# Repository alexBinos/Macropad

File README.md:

# Macropad

A 20 key macro-keyboard with extra hardware features including;

- 1x rotary encoder
- I2C breakout to support an OLED display
- Per-key RGB LED lighting and underglow lighting
- Hot-swap key switch sockets
- 4 port USB 2.0 HUB with 3 spare downstream ports

<br>

Power for the board and downstream USB ports is sourced from the upstream USB port. The board consumes 62mA with all LEDs powered off giving 438mA to be shared among the remaining 3 USB ports. With all LEDs powered up to pixel value 128 (recommended maximum) the board consumes 264mA.

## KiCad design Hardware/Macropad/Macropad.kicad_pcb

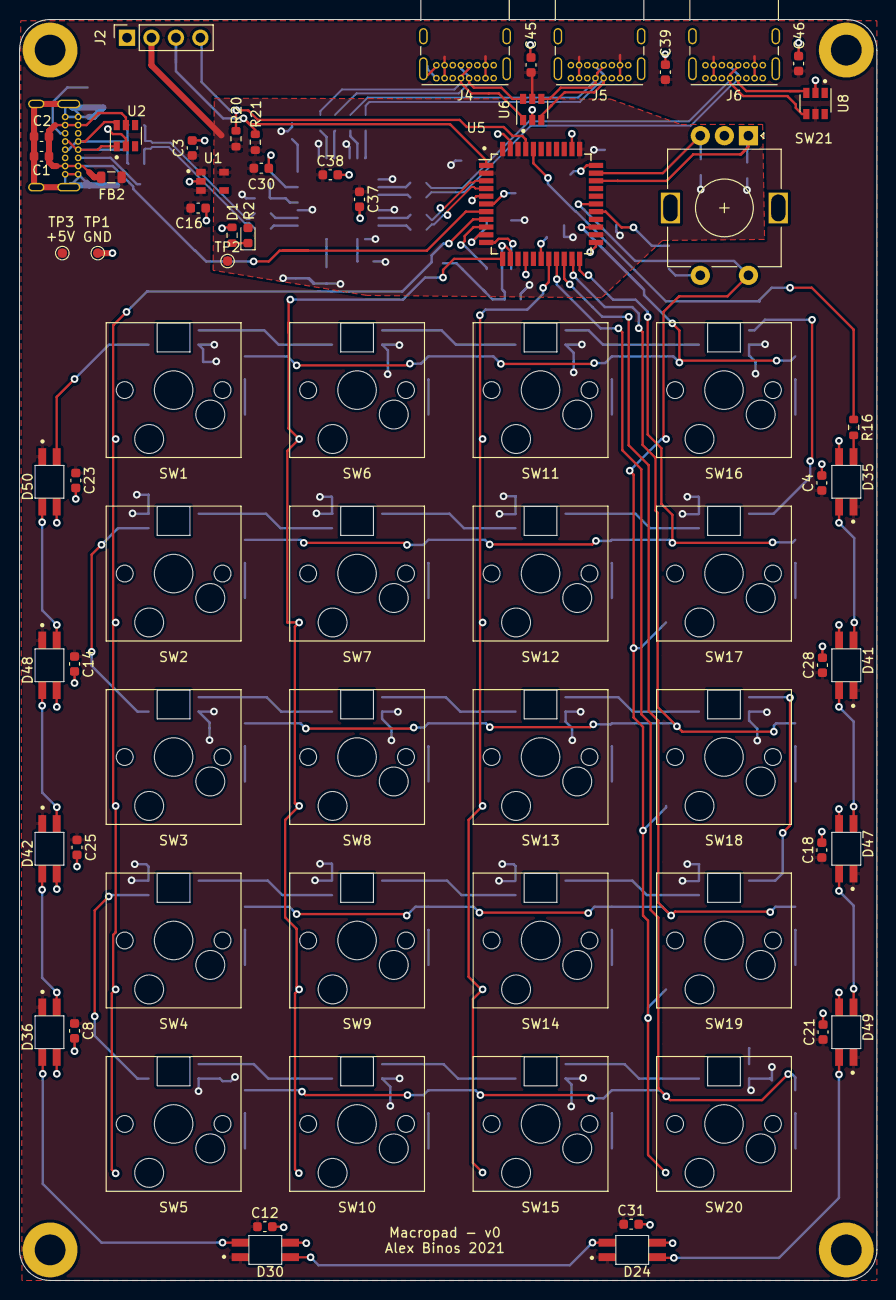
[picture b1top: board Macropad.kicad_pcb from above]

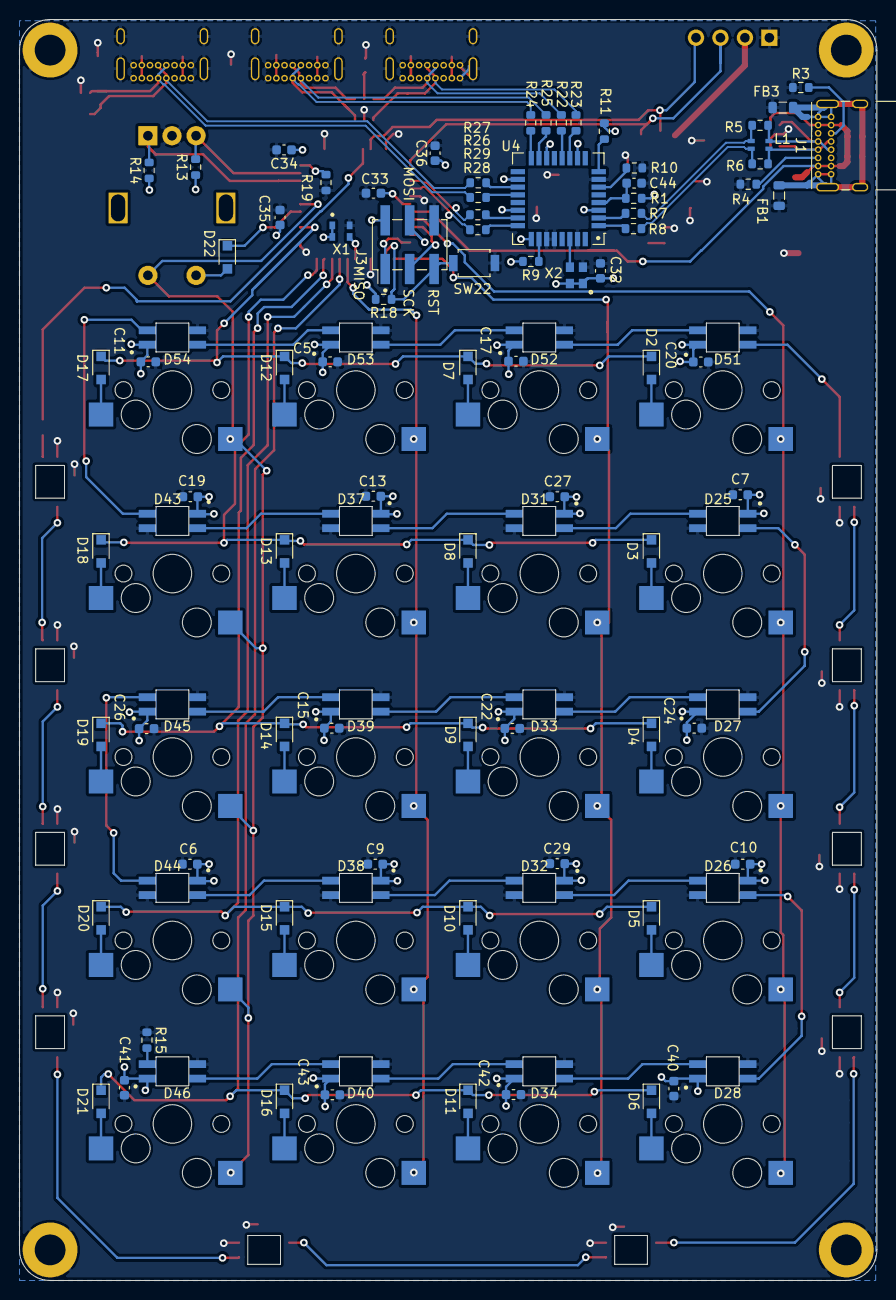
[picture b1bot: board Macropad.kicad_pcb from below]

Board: 2 copper layers, 89.0 x 130.9 mm, 172 parts (89 on the bottom side), 109 nets.

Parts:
C1: 10uF; C_0603_1608Metric
C2, C30, C33, C36, C37, C39, C44, C45, C46: 1uF; C_0603_1608Metric
C3, C4, C5, C6, C7, C8, C9, C10, C11, C12, C13, C14, C15, C16, C17, C18, C19, C20, C21, C22, C23, C24, C25, C26, C27, C28, C29, C31, C32, C34, C35, C38, C40, C41, C42, C43: 100nF; C_0603_1608Metric
D1: LED; D_0603_1608Metric
D2, D3, D4, D5, D6, D7, D8, D9, D10, D11, D12, D13, D14, D15, D16, D17, D18, D19, D20, D21, D22: D; SOD323_HS
D24: UG_LED_4; SK6812-MINI-E
D25: K30; SK6812-MINI-E
D26: K10; SK6812-MINI-E
D27: K20; SK6812-MINI-E
D28: K00; SK6812-MINI-E
D30: UG_LED_5; SK6812-MINI-E
D31: K31; SK6812-MINI-E
D32: K11; SK6812-MINI-E
D33: K21; SK6812-MINI-E
D34: K01; SK6812-MINI-E
D35: UG_LED_0; SK6812-MINI-E
D36: UG_LED_6; SK6812-MINI-E
D37: K32; SK6812-MINI-E
D38: K12; SK6812-MINI-E
D39: K22; SK6812-MINI-E
D40: K02; SK6812-MINI-E
D41: UG_LED_1; SK6812-MINI-E
D42: UG_LED_7; SK6812-MINI-E
D43: K33; SK6812-MINI-E
D44: K13; SK6812-MINI-E
D45: K23; SK6812-MINI-E
D46: K03; SK6812-MINI-E
D47: UG_LED_2; SK6812-MINI-E
D48: UG_LED_8; SK6812-MINI-E
D49: UG_LED_3; SK6812-MINI-E
D50: UG_LED_9; SK6812-MINI-E
D51: K40; SK6812-MINI-E
D52: K41; SK6812-MINI-E
D53: K42; SK6812-MINI-E
D54: K43; SK6812-MINI-E
FB1, FB2, FB3: Ferrite_Bead; L_0805_2012Metric
H1, H2, H3, H4: MountingHole_Pad; MountingHole_3.2mm_M3_ISO7380_Pad
J1, J4, J5, J6: USB_C_Receptacle_USB2.0; USB_C_Receptacle_GCT_USB4085
J2: Conn_01x04_Female; PinSocket_1x04_P2.54mm_Vertical
J3: Conn_02x03_Odd_Even; PinHeader_2x03_P2.54mm_Vertical_SMD
L1: L_Core_Iron_Coupled_1423; SMM2012E
R1, R9, R10, R11, R13, R14, R18, R19, R20, R21: 4K7; R_0603_1608Metric
R2: 330R; R_0603_1608Metric
R3, R4: 5K1; R_0603_1608Metric
R5, R6: OPT; R_0603_1608Metric
R7, R8, R22, R23, R24, R25, R26, R27, R28, R29: 22R; R_0603_1608Metric
R15, R16: Rt; R_0603_1608Metric
SW1: K40_1U; CherryMX_1.00u_PCB_KailhSocket
SW2: K30_1U; CherryMX_1.00u_PCB_KailhSocket
SW3: K20_1U; CherryMX_1.00u_PCB_KailhSocket
SW4: K10_1U; CherryMX_1.00u_PCB_KailhSocket
SW5: K00_1U; CherryMX_1.00u_PCB_KailhSocket
SW6: K41_1U; CherryMX_1.00u_PCB_KailhSocket
SW7: K31_1U; CherryMX_1.00u_PCB_KailhSocket
SW8: K21_1U; CherryMX_1.00u_PCB_KailhSocket
SW9: K11_1U; CherryMX_1.00u_PCB_KailhSocket
SW10: K01_1U; CherryMX_1.00u_PCB_KailhSocket
SW11: K42_1U; CherryMX_1.00u_PCB_KailhSocket
SW12: K32_1U; CherryMX_1.00u_PCB_KailhSocket
SW13: K22_1U; CherryMX_1.00u_PCB_KailhSocket
SW14: K12_1U; CherryMX_1.00u_PCB_KailhSocket
SW15: K02_1U; CherryMX_1.00u_PCB_KailhSocket
SW16: K43_1U; CherryMX_1.00u_PCB_KailhSocket
SW17: K33_1U; CherryMX_1.00u_PCB_KailhSocket
SW18: K23_1U; CherryMX_1.00u_PCB_KailhSocket
SW19: K13_1U; CherryMX_1.00u_PCB_KailhSocket
SW20: K03_1U; CherryMX_1.00u_PCB_KailhSocket
SW21: Rotary_Encoder_Switch; RotaryEncoder_Alps_EC11E-Switch_Vertical_H20mm
SW22: SW_Push; SW_SPST_B3U-1000P
TP1, TP2, TP3: TestPoint; TestPoint_Pad_D1.0mm
U1: TCR2EF33; TCR2EF33_SOT25
U2, U6, U8: SRV05-4; SOT-23-6
U4: TUSB2046b
U5: ATmega32U4-AU; TQFP-44_10x10mm_P0.8mm
X1: KC2016K
X2: 625L3C006M00000

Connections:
+3V3: C30.1, C32.1, C34.1, C35.1, C36.1, C37.1, C38.1, D1.2, J2.2, J3.2, R1.2, R9.2, R11.2, R13.1, R14.1, R18.1, R20.1, R21.1, TP2.1, U1.5, U4.3, U4.10, U4.14, U4.18, U4.22, U4.25, U5.2, U5.14, U5.24, U5.34, U5.42, U5.44, X1.1, X1.4, X2.1, X2.4
+5V: C3.1, C4.1, C5.1, C6.1, C7.1, C8.1, C9.1, C10.1, C11.1, C12.1, C13.1, C14.1, C15.1, C16.1, C17.1, C18.1, C19.1, C20.1, C21.1, C22.1, C23.1, C24.1, C25.1, C26.1, C27.1, C28.1, C29.1, C31.1, C39.1, C40.1, C41.1, C42.1, C43.1, C45.1, C46.1, D24.1, D25.1, D26.1, D27.1, D28.1, D30.1, D31.1, D32.1, D33.1, D34.1, D35.1, D36.1, D37.1, D38.1, D39.1, D40.1, D41.1, D42.1, D43.1, D44.1, D45.1, D46.1, D47.1, D48.1, D49.1, D50.1, D51.1, D52.1, D53.1, D54.1, FB2.1, J4.A4, J4.A9, J4.B4, J4.B9, J5.A4, J5.A9, J5.B4, J5.B9, J6.A4, J6.A9, J6.B4, J6.B9, TP3.1, U1.1, U1.3, U6.5, U8.5
/USB/D+: L1.2, R6.1, R8.2
/USB/D-: L1.1, R5.1, R7.2
/USB_HUB/D1+: R22.2, U4.12
/USB_HUB/D1-: R23.2, U4.11
/USB_HUB/D2+: R24.2, U4.16
/USB_HUB/D2-: R25.2, U4.15
/USB_HUB/D3+: R26.2, U4.20
/USB_HUB/D3-: R27.2, U4.19
/USB_HUB/D4+: R28.2, U4.24
/USB_HUB/D4-: R29.2, U4.23
COL[0]: SW1.2, SW2.2, SW3.2, SW4.2, SW5.2, U5.8
COL[1]: SW6.2, SW7.2, SW8.2, SW9.2, SW10.2, U5.12
COL[2]: SW11.2, SW12.2, SW13.2, SW14.2, SW15.2, U5.18
COL[3]: SW16.2, SW17.2, SW18.2, SW19.2, SW20.2, SW21.S2, U5.28
GND: C3.2, C4.2, C5.2, C6.2, C7.2, C8.2, C9.2, C10.2, C11.2, C12.2, C13.2, C14.2, C15.2, C16.2, C17.2, C18.2, C19.2, C20.2, C21.2, C22.2, C23.2, C24.2, C25.2, C26.2, C27.2, C28.2, C29.2, C30.2, C31.2, C32.2, C33.2, C34.2, C35.2, C36.2, C37.2, C38.2, C39.2, C40.2, C41.2, C42.2, C43.2, C44.1, C45.2, C46.2, D24.3, D25.3, D26.3, D27.3, D28.3, D30.3, D31.3, D32.3, D33.3, D34.3, D35.3, D36.3, D37.3, D38.3, D39.3, D40.3, D41.3, D42.3, D43.3, D44.3, D45.3, D46.3, D47.3, D48.3, D49.3, D50.3, D51.3, D52.3, D53.3, D54.3, FB1.1, FB3.1, H1.1, H2.1, H3.1, H4.1, J2.1, J3.6, J4.A1, J4.A12, J4.B1, J4.B12, J4.S1, J5.A1, J5.A12, J5.B1, J5.B12, J5.S1, J6.A1, J6.A12, J6.B1, J6.B12, J6.S1, R2.1, R3.1, R4.1, R10.1, R15.1, R19.2, SW21.C, SW22.2, TP1.1, U1.2, U2.2, U4.7, U4.27, U4.28, U4.31, U5.5, U5.15, U5.23, U5.35, U5.43, U6.2, U8.2, X1.2, X2.2
MISO: J3.1, U5.11
MOSI: J3.4, U5.10
unnamed: C1.2, C2.2, FB1.2, FB3.2, J1.A1, J1.A12, J1.B1, J1.B12, J1.S1
unnamed: C33.1, U5.6
unnamed: C44.2, R1.1, U4.4
unnamed: D1.1, R2.2
unnamed: D2.2, SW1.1
unnamed: D3.2, SW2.1
unnamed: D4.2, SW3.1
unnamed: D5.2, SW4.1
unnamed: D6.2, SW5.1
unnamed: D7.2, SW6.1
unnamed: D8.2, SW7.1
unnamed: D9.2, SW8.1
unnamed: D10.2, SW9.1
unnamed: D11.2, SW10.1
unnamed: D12.2, SW11.1
unnamed: D13.2, SW12.1
unnamed: D14.2, SW13.1
unnamed: D15.2, SW14.1
unnamed: D16.2, SW15.1
unnamed: D17.2, SW16.1
unnamed: D18.2, SW17.1
unnamed: D19.2, SW18.1
unnamed: D20.2, SW19.1
unnamed: D21.2, SW20.1
unnamed: D22.2, SW21.S1
unnamed: D24.2, D30.4
unnamed: D25.2, D27.4
unnamed: D25.4, D31.2
unnamed: D26.2, D28.4
unnamed: D26.4, D32.2
unnamed: D27.2, D33.4
unnamed: D28.2, D34.4
unnamed: D30.2, D36.4
unnamed: D31.4, D37.2
unnamed: D32.4, D38.2
unnamed: D33.2, D39.4
unnamed: D34.2, D40.4
unnamed: D35.2, D41.4
unnamed: D35.4, R16.2
unnamed: D36.2, D42.4
unnamed: D37.4, D43.2
unnamed: D38.4, D44.2
unnamed: D39.2, D45.4
unnamed: D40.2, D46.4
unnamed: D41.2, D47.4
unnamed: D42.2, D48.4
unnamed: D43.4, D54.2
unnamed: D44.4, D45.2
unnamed: D46.2, R15.2
unnamed: D47.2, D49.4
unnamed: D48.2, D50.4
unnamed: D51.2, D52.4
unnamed: D52.2, D53.4
unnamed: D53.2, D54.4
unnamed: J1.A5, R4.2
unnamed: J1.A6, J1.B6, L1.3, R6.2, U2.1
unnamed: J1.A7, J1.B7, L1.4, R5.2, U2.6
unnamed: J1.B5, R3.2
unnamed: R9.1, U4.26
unnamed: R10.2, U4.6
unnamed: R11.1, U4.8
unnamed: R19.1, U5.33
unnamed: U4.30, X2.3
unnamed: U5.17, X1.3
RGB[0]: D24.4, D49.2
RGB[1]: D50.2, D51.4
RGB_OUT: R16.1, U5.40
ROT_ENC_A: R14.2, SW21.A, U5.31
ROT_ENC_B: R13.2, SW21.B, U5.32
ROW[0]: D6.1, D11.1, D16.1, D21.1, U5.19
ROW[1]: D5.1, D10.1, D15.1, D20.1, U5.20
ROW[2]: D4.1, D9.1, D14.1, D19.1, U5.21
ROW[3]: D3.1, D8.1, D13.1, D18.1, U5.22
ROW[4]: D2.1, D7.1, D12.1, D17.1, U5.25
ROW[5]: D22.1, U5.27
RST: J3.5, R18.2, SW22.1, U5.13
SCK: J3.3, U5.9
SCL: J2.3, R21.2, U5.1
SDA: J2.4, R20.2, U5.41
USB_D0+: R8.1, U4.1
USB_D0-: R7.1, U4.2
USB_D1+: J4.A6, J4.B6, R22.1, U6.6
USB_D1-: J4.A7, J4.B7, R23.1, U6.1
USB_D2+: J5.A6, J5.B6, R24.1, U6.3
USB_D2-: J5.A7, J5.B7, R25.1, U6.4
USB_D3+: J6.A6, J6.B6, R26.1, U8.3
USB_D3-: J6.A7, J6.B7, R27.1, U8.4
USB_D4+: R28.1, U5.4
USB_D4-: R29.1, U5.3
VBUS: C1.1, C2.1, FB2.2, J1.A4, J1.A9, J1.B4, J1.B9, U2.5, U5.7

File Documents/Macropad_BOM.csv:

Id,Designator,Package,Quantity,Designation,Supplier and ref
1,SW22,SW_SPST_B3U-1000P,1,SW_Push,
2,D54;D53;D52;D51;D50;D49;D48;D47;D46;D45;D44;D43;D42;D41;D40;D39;D38;D37;D36;D35;D34;D33;D32;D31;D30;D28;D27;D26;D25;D24;,SK6812-MINI-E,30,,
3,TP2;TP3;TP1,TestPoint_Pad_D1.0mm,3,TestPoint,
4,C30;C39;C46;C45;C37;C44;C2;C36;C33,C_0603_1608Metric,9,1uF,
5,C16;C20;C14;C23;C38;C43;C42;C41;C40;C3;C35;C34;C32;C31;C29;C28;C27;C26;C25;C24;C22;C21;C19;C18;C17;C15;C13;C12;C11;C10;C9;C8;C7;C6;C5;C4,C_0603_1608Metric,36,100nF,
6,U8;U6;U2,SOT-23-6,3,SRV05-4,
7,J5;J6;J4;J1,USB_C_Receptacle_GCT_USB4085,4,USB_C_Receptacle_USB2.0,
8,FB3;FB2;FB1,L_0805_2012Metric,3,Ferrite_Bead,
9,SW12;SW7;SW17;SW2;SW16;SW18;SW8;SW11;SW6;SW13;SW3;SW1;SW20;SW19;SW15;SW14;SW10;SW9;SW5;SW4;,CherryMX_1.00u_PCB_KailhSocket,20,,
10,J3,PinHeader_2x03_P2.54mm_Vertical_SMD,1,Conn_02x03_Odd_Even,
11,U4,TUSB2046b,1,TUSB2046b,
12,R1;R13;R11;R10;R9;R21;R20;R19;R18;R14,R_0603_1608Metric,10,4K7,
13,U5,TQFP-44_10x10mm_P0.8mm,1,ATmega32U4-AU,
14,X2,625L3C006M00000,1,625L3C006M00000,
15,R29;R28;R27;R26;R25;R24;R23;R22;R8;R7,R_0603_1608Metric,10,22R,
16,R6;R5,R_0603_1608Metric,2,OPT,
17,R4;R3,R_0603_1608Metric,2,5K1,
18,R2,R_0603_1608Metric,1,330R,
19,L1,SMM2012E,1,L_Core_Iron_Coupled_1423,
20,D1,D_0603_1608Metric,1,LED,
21,C1,C_0603_1608Metric,1,10uF,
22,D22;D21;D20;D19;D18;D17;D16;D15;D14;D13;D12;D11;D10;D9;D8;D7;D6;D5;D4;D3;D2,SOD323_HS,21,D,
23,X1,KC2016K,1,KC2016K,
24,U1,TCR2EF33_SOT25,1,TCR2EF33,
25,SW21,RotaryEncoder_Alps_EC11E-Switch_Vertical_H20mm,1,Rotary_Encoder_Switch,
26,R16;R15,R_0603_1608Metric,2,Rt,
27,J2,PinSocket_1x04_P2.54mm_Vertical,1,Conn_01x04_Female,

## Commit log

2021-08-12 Updating project description
2021-08-13 Bulk of the schematic done
2021-08-14 Schematic mostly done. Started grouping components in layout
2021-08-15 First pass of the layout done
2021-08-18 Redoing layout with key switches upside down for better LED placement
2021-08-19 Layout done, cleaned up schematic and generated gerbers
2021-08-19 removing redundant layout files
2021-09-11 Updating 3D models, mapping models for USB and encoder
2021-09-11 Adding schematic pdf
2021-09-12 Adding board DXFs
2021-09-12 Updating git ignore
2021-09-12 Adding frame file and board 3D model
2021-09-12 Removing csv from gitignore
2021-09-12 Fixing a naming mistake in schematic
2021-09-12 Adding BOM
2021-09-14 Adding part description field to BOM
2021-09-17 Adding firmware files
2021-09-22 Starting custom matrix scanning, using QMK default scanning algorithm as a starting point
2021-10-30 Adding supporting members
2021-10-30 Standard keymap
2021-10-30 Including DFU reset button in mechanical assembly
2022-05-12 Updating for 3D printing and to fix clashes
2022-05-12 Moving hardware files to v1 directory
2022-05-12 Adding hardware v2 project
2022-05-18 Updating hardware version numbers
2022-05-18 Removing v2
2022-05-18 Removing gerbers
2022-05-18 Updating git ignore to include .zip
2022-05-18 Adding USB 2.0 physical layer app note
2022-05-18 Adding USB termination, moving I2C lines to TWI pins
2022-05-19 Moving underglow LED and USB VBUS decoupling caps
2022-05-19 Connected USB resistors
2022-05-21 Disconecting mounting holes from ground Adding schmitt trigger bugger to USB HUB reset Cleaning up routing and fixing plane connections
2022-05-21 Fixing silk clashes
2022-05-21 Adding LED power draw spreadsheet
2022-08-07 v1 gerbers
2022-08-08 Generating v1 schematic
2022-08-08 Removing old pdf
2022-08-08 Adding change documents
2022-08-08 Updating v0 and v1 firmware
2022-08-08 binaries
2022-08-09 Fixing typo
2022-08-10 Updating README
2022-09-10 Adding USB fix images
